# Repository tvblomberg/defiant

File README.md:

# Defiant

A 36-key wireless split keyboard inspired by the ZSA Voyager and GEIST Totem.

## Design Goals

- 36 keys (5 columns x 3 rows + 1 side key + 2 thumb keys per half)
- MX key spacing (19.05mm)
- Choc switches with hotswap sockets
- Wireless split via Seeed XIAO nRF52840
- ZMK firmware
- 3D printed case
- Ergogen-generated PCB

## Layout

The main matrix uses a Voyager-inspired column stagger with a Totem-style outer side key. The thumb cluster is a 2-key rotated cluster.

## Versions

Each hardware revision lives in its own self-contained directory:

- `v1/` — first release (built 2026-04-19): Choc switches, nice!nano v2, no display, ~110 mAh battery
- `v2/` — adds nice!view per-half display, 750 mAh battery, canonical MCU-on-top assembly

All commands below run from inside the version directory you're working on (e.g. `cd v1`).

### v2 assembly notes

- **nice!nano**: socketed via Mill-Max headers, mounted on the **F (top)** side. Bridge the F-side MCU jumpers.
- **Switches, hotswaps, diodes, JST connector, power switch, reset switch**: all on the **B (bottom)** side.
- **Battery**: 750 mAh 403450 LiPo (4 × 34 × 50 mm). Sits below the PCB inside a case cavity — case must accommodate the keep-out.
- **nice!view display**: mounted on F (top), anchored at the same point as the MCU so the display's pin row sits dead-center over the nano body. SPI uses D5/D6/D7 for CS/MOSI/SCK (custom overlay; the upstream `nice_view_adapter` would collide with the matrix columns). Charge status is read off the on-screen battery widget.

## Building

### Prerequisites

- Node.js
- OpenSCAD (for test plate STL export)
- KiCad 8 (for PCB editing)

### Generate Ergogen output

```bash
cd v1
npm install
npx ergogen . -o output --debug
```

### Generate test plate

```bash
cd v1
python3 generate_plate.py
```

Opens `output/test_plate.scad` in OpenSCAD to export STL for 3D printing.

## Project Structure

```
.github/workflows/   # ZMK firmware CI (per-version build job)
freerouting.jar      # Shared autorouter (gitignored)
v1/
  config.yaml        # Ergogen keyboard layout definition
  generate_plate.py  # Test plate generator
  footprints/        # Ergogen footprint submodules (pinned per version)
  firmware/          # ZMK shield + build matrix
  releases/          # Tagged PCB releases
  output/            # Generated files (gitignored)
```

## License

This project is licensed under [CC BY-NC-SA 4.0](LICENSE). You are free to build one for personal use, but commercial sale is not permitted.

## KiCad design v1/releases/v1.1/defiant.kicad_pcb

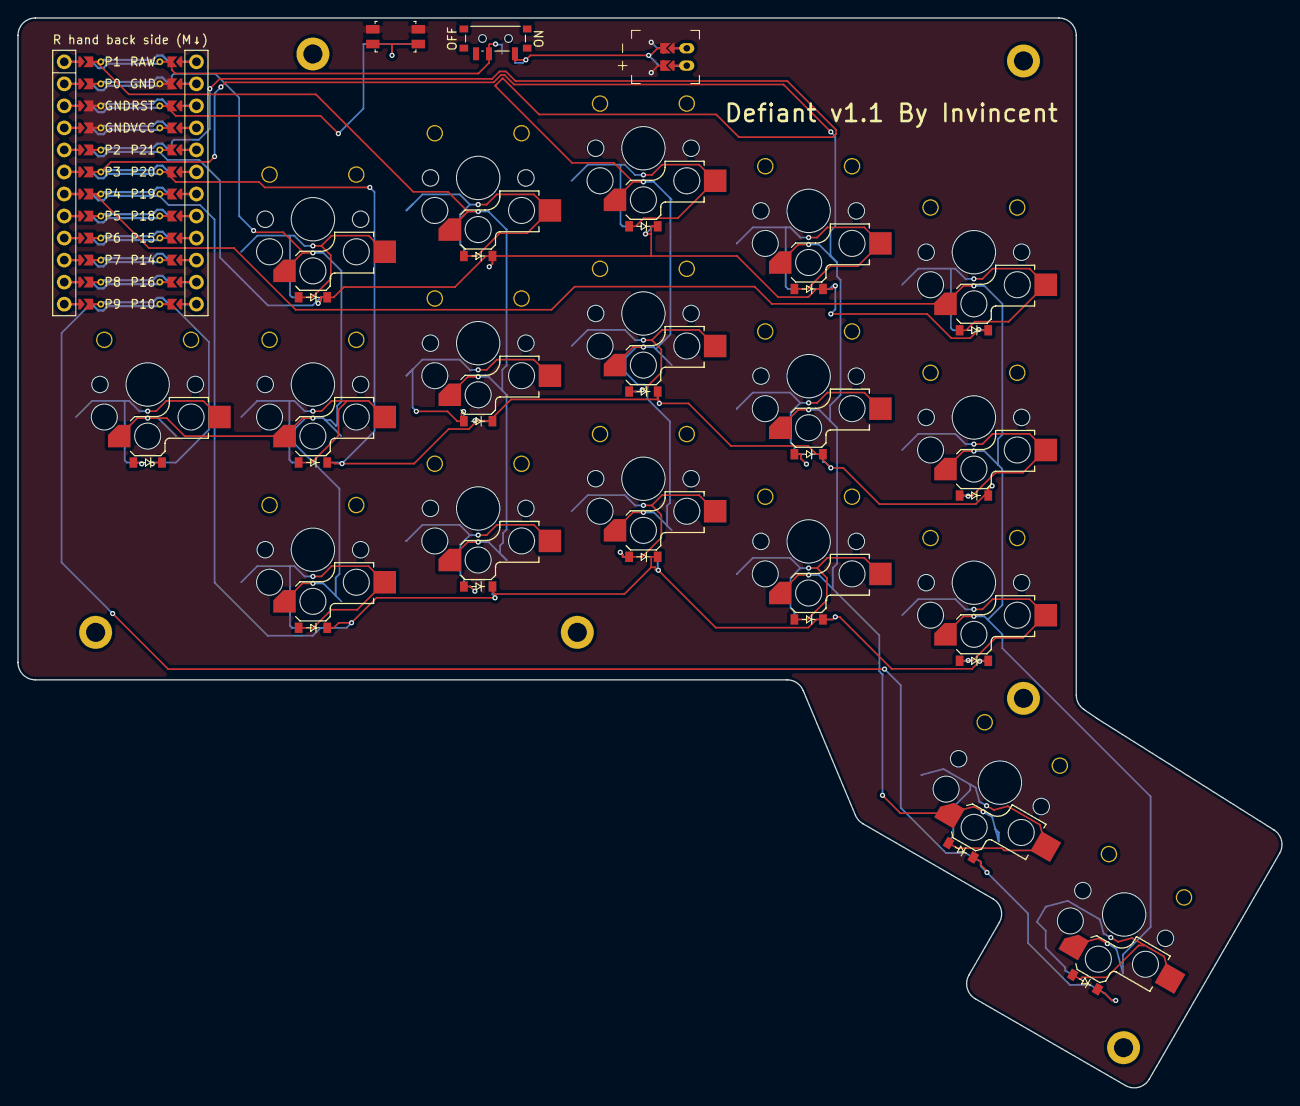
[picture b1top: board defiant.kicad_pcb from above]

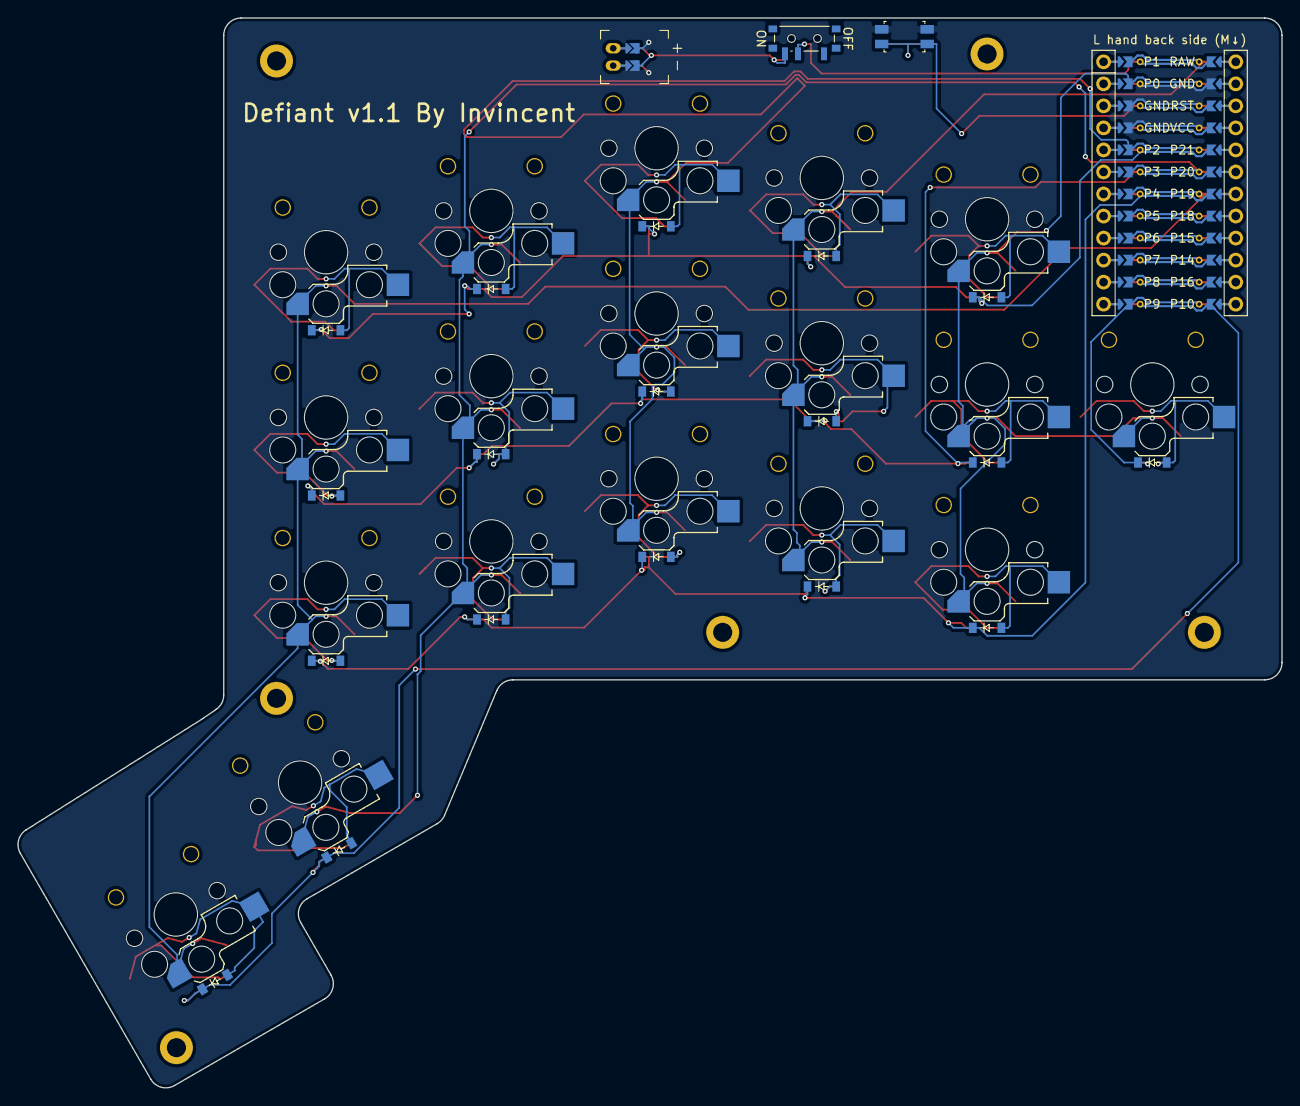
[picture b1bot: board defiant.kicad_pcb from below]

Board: 2 copper layers, 145.7 x 123.3 mm, 46 parts (18 on the bottom side), 34 nets.

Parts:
D1, D2, D3, D4, D5, D6, D7, D8, D9, D10, D11, D12, D13, D14, D15, D16, D17, D18: diode_tht_sod123
H1, H2, H3, H4, H5, H6: mounting_hole_plated
JST1: battery_connector_jst_ph_2
MCU1: mcu_nice_nano
PWR1: power_switch_smd_side
RST1: reset_switch_smd_side
S1, S2, S3, S4, S5, S6, S7, S8, S9, S10, S11, S12, S13, S14, S15, S16, S17, S18: switch_choc_v1_v2

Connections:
BAT_P: JST1.1, PWR1.1, PWR1.3
GND: JST1.2, MCU1.102, MCU1.121, MCU1.122, RST1.1, RST1.3
JST1_1: JST1.11, JST1.21, JST1.31
JST1_2: JST1.12, JST1.22, JST1.32
P0: MCU1.123, S1.1, S2.1, S3.1, S16.1
P1: MCU1.124, S4.1, S5.1, S6.1
P2: MCU1.120, S7.1, S8.1, S9.1
P3: MCU1.119, S10.1, S11.1, S12.1, S17.1
P4: MCU1.118, S13.1, S14.1, S15.1, S18.1
P9: D16.1, MCU1.113
P10: D17.1, D18.1, MCU1.112
P19: D1.1, D4.1, D7.1, D10.1, D13.1, MCU1.107
P20: D2.1, D5.1, D8.1, D11.1, D14.1, MCU1.106
P21: D3.1, D6.1, D9.1, D12.1, D15.1, MCU1.105
RAW: MCU1.101, PWR1.2
RST: MCU1.103, RST1.2, RST1.4
far_thumb: D18.2, S18.2
index_bottom: D10.2, S10.2
index_home: D11.2, S11.2
index_top: D12.2, S12.2
inner_bottom: D13.2, S13.2
inner_home: D14.2, S14.2
inner_top: D15.2, S15.2
middle_bottom: D7.2, S7.2
middle_home: D8.2, S8.2
middle_top: D9.2, S9.2
near_thumb: D17.2, S17.2
outer_default: D16.2, S16.2
pinky_bottom: D1.2, S1.2
pinky_home: D2.2, S2.2
pinky_top: D3.2, S3.2
ring_bottom: D4.2, S4.2
ring_home: D5.2, S5.2
ring_top: D6.2, S6.2

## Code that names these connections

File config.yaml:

units:
  # MX spacing
  kx: 19.05
  ky: 19.05
  # Padding for board outline
  px: kx + 4
  py: ky + 4

points:
  key:
    spread: kx
    padding: ky
    tags:
      key: true

  zones:
    # Main 5x3 matrix - Voyager stagger
    # Columns P0-P4 (left side of nice!nano)
    # Rows P19-P21, P10 (right side of nice!nano) for better routing
    # R3 (P10) is used for side key and thumb keys
    matrix:
      anchor:
        shift: [100, -200]
      columns:
        pinky:
          key.column_net: P0
        ring:
          key.stagger: 0.25 ky
          key.column_net: P1
        middle:
          key.stagger: 0.25 ky - 1.34
          key.column_net: P2
        index:
          key.stagger: -0.25 ky - 2.46
          key.column_net: P3
        inner:
          key.stagger: -0.25 ky
          key.column_net: P4
      rows:
        bottom:
          row_net: P19
        home:
          row_net: P20
        top:
          row_net: P21

    # Totem-style side key (outer pinky)
    # Shares column P0 with pinky, uses dedicated row P9
    # (P9 is bottom-left of nice!nano, physically near the side key)
    side:
      anchor:
        ref: matrix_pinky_home
        shift: [-kx, 0]
      columns:
        outer:
          key.column_net: P0
      rows:
        default:
          row_net: P9
      key.tags:
        key: true
        side: true

    # Thumb cluster - 2 keys
    # near shares column P3 (index), far shares column P4 (inner)
    # Both use row P10 (R3)
    thumb:
      anchor:
        ref: matrix_inner_bottom
        shift: [3, -kx - 4]
        rotate: -30
      columns:
        near:
          key.column_net: P3
        far:
          key.spread: 20
          key.stagger: -6
          key.width: 1.5 kx
          key.column_net: P4
      rows:
        thumb:
          row_net: P10
      key.tags:
        key: true
        thumb: true

outlines:
  # Key switch cutouts (MX plate cutout = 14mm)
  _keys:
    - what: rectangle
      where: key
      size: [14, 14]

  # Keycap outlines
  _caps:
    - what: rectangle
      where: key
      size: [18, 18]
    - what: rectangle
      where: /^thumb_far/
      size: [18, 1.5 ky - 1]
      operation: stack

  # Keycaps only
  preview_caps:
    - what: outline
      name: _caps

  # Switches only
  preview_switches:
    - what: outline
      name: _keys

  # Both layers combined
  preview:
    - what: outline
      name: _caps
    - what: outline
      name: _keys
      operation: stack
  raw:
  - what: rectangle
    where: true
    size: [px, py]
  board:
  - what: polygon
    operation: stack
    fillet: 2
    points:
      # All points relative to matrix_pinky_bottom (100, -200)
      # Key positions: side(80.95,-180.95) pinky_top(100,-161.9)
      #   middle_top(157.2,-153.71) inner_top(195.2,-165.7)
      #   inner_bottom(195.2,-203.8) pinky_bottom(100,-200)
      #   thumb_near(198.2,-226.85,r-30) thumb_far(212.6,-242.05,r-30)
      #
      # Padding: 12mm from key centers (~half key + 3mm)
      #
      # 1. Top-left (3mm from keycap edges)
      - ref: matrix_pinky_bottom
        shift: [-34, 61.3]
      # 2. Top-right
      - ref: matrix_pinky_bottom
        shift: [88, 61.3]
      # 3. Right side down to inner bottom
      - ref: matrix_pinky_bottom
        shift: [88, -17.8]
      # 4. Into thumb - right side of near thumb
      - ref: thumb_near_thumb
        shift: [6, 12]
      # 5. Right side of far thumb (extra padding for 1.5u height)
      - ref: thumb_far_thumb
        shift: [12, 17]
      # 6. Bottom of far thumb
      - ref: thumb_far_thumb
        shift: [12, -17]
      # 7. Left of far thumb
      - ref: thumb_far_thumb
        shift: [-12, -17]
      - ref: thumb_far_thumb
        shift: [-12, -6]
      # 8. Left of near thumb
      - ref: thumb_near_thumb
        shift: [-12, -12]
      # 9. Bottom-right of main body (3mm from keycap edges)
      - ref: matrix_pinky_bottom
        shift: [56, -15]
      # 10. Bottom-left
      - ref: matrix_pinky_bottom
        shift: [-34, -15]
  combo:
    - name: board
    - operation: subtract
      name: preview_caps
  plate:
    - name: board
    - operation: subtract
      name: _keys

pcbs:
  defiant:
    template: kicad8
    outlines:
      main:
        outline: board
        layer: Edge.Cuts
    footprints:
      # Choc hotswap switches at every key position
      choc_hotswap:
        what: ceoloide/switch_choc_v1_v2
        where: key
        params:
          hotswap: true
          reversible: true
          keycap_width: 18
          keycap_height: 18
          from: "{{column_net}}"
          to: "{{colrow}}"
        adjust:
          rotate: 180

      # Diodes for switch matrix
      diode:
        what: ceoloide/diode_tht_sod123
        where: key
        params:
          reversible: true
          from: "{{colrow}}"
          to: "{{row_net}}"
        adjust:
          shift: [0, -9]
          rotate: 180

      # nice!nano MCU - upper left, USB-C facing top edge
      mcu:
        what: ceoloide/mcu_nice_nano
        where:
          ref: side_outer
          shift: [-2, 24.5]
          rotate: 0
        params:
          reversible: true
          reverse_mount: true

      # Battery connector (JST PH 2.0) - left side below XIAO
      battery:
        what: ceoloide/battery_connector_jst_ph_2
        where:
          ref: matrix_middle_top
          shift: [0 + 5, ky / 2 + 1]
          rotate: 270
        params:
          reversible: true

      # Power switch - near XIAO, top left, rotated horizontal
      power:
        what: ceoloide/power_switch_smd_side
        where:
          ref: matrix_ring_top
          shift: [2, ky - 3]
          rotate: 90
        params:
          reversible: true
          from: BAT_P
          to: RAW

      # Reset button - near XIAO, top left
      reset:
        what: ceoloide/reset_switch_smd_side
        where:
          ref: matrix_pinky_top
          shift: [kx / 2, ky + 2]
          rotate: 0
        params:
          reversible: true
          from: GND
          to: RST

      # Silkscreen text
      board_name:
        what: ceoloide/utility_text
        where:
          ref: matrix_inner_top
          shift: [-0.5 kx, ky - 3]
        params:
          text: "Defiant v1.1 By Invincent"
          height: 2
          width: 2
          thickness: 0.3
          reversible: true

      # Ground fill on both sides
      ground_fill:
        what: ceoloide/utility_filled_zone
        where:
          ref: matrix_middle_home
        params:
          side: "F&B"
          net: GND

      # Mounting holes (M2)
      mount_top_left:
        what: ceoloide/mounting_hole_plated
        where:
          ref: matrix_pinky_top
          shift: [0, ky]

      mount_top_right:
        what: ceoloide/mounting_hole_plated
        where:
          ref: matrix_inner_top
          shift: [.3 kx, ky + 3]

      mount_bottom_left:
        what: ceoloide/mounting_hole_plated
        where:
          ref: matrix_pinky_bottom
          shift: [1.6 kx, -0.5 ky]

      mount_bottom_right:
        what: ceoloide/mounting_hole_plated
        where:
          ref: matrix_inner_bottom
          shift: [0.3 kx, -0.7 ky]

      mount_side:
        what: ceoloide/mounting_hole_plated
        where:
          ref: side_outer
          shift: [-6, -1.5 ky]

      mount_thumb:
        what: ceoloide/mounting_hole_plated
        where:
          ref: thumb_far_thumb
          shift: [ 0.4 kx, -0.7 ky]

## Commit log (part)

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2026-03-30 Initial commit: Ergogen layout for Defiant keyboard
    Voyager-inspired 36-key split wireless layout with Totem-style
    side key, MX spacing, and test plate generator for verification.
2026-03-30 license
2026-03-30 readme
2026-03-31 Add PCB scaffold with components, board outline, and optimized matrix
    - Added Choc hotswap switch, diode, XIAO nRF52840, battery connector,
    power switch, and reset button footprints via Ergogen
    - Optimized key matrix from 13 nets to 9 (6 cols x 3 rows) to fit
    within XIAO's 11 GPIO pins
    - Refined column stagger based on physical measurements
    - Added Voyager-style board outline with thumb cluster extension
2026-03-31 More board tweaking
2026-04-01 move things around
2026-04-08 Version 1 of the keyboard
2026-04-25 Reorganize into v1/ subdir to support multiple hardware revisions
    Each hardware version becomes a self-contained directory holding its own
    Ergogen config, footprint submodule pins, ZMK shield, and releases. v2
    work can branch from a copy of v1/ without disturbing the shipped design.
